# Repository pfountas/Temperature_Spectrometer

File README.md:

# Temperature Spectrometer
Temperature Spectrometer based on the NXP mbed LPC1768 platform.

This is an embedded digital temperature spectrometer with logging capabilities. The system was based on the NXP mbed LPC1768 platform. The microcontroller used in the temperature logger is based on the 32-bit ARM Cortex-M3 microcontroller with 512 kB flash and 64 kB SRAM. The microcontroller was connected to a TMP102 temperature sensor using an I2C interface and to an LCD screen using an SPI interface. The system supports real-time temperature spectrum computation and control and data export through an on-board USB UART connection.

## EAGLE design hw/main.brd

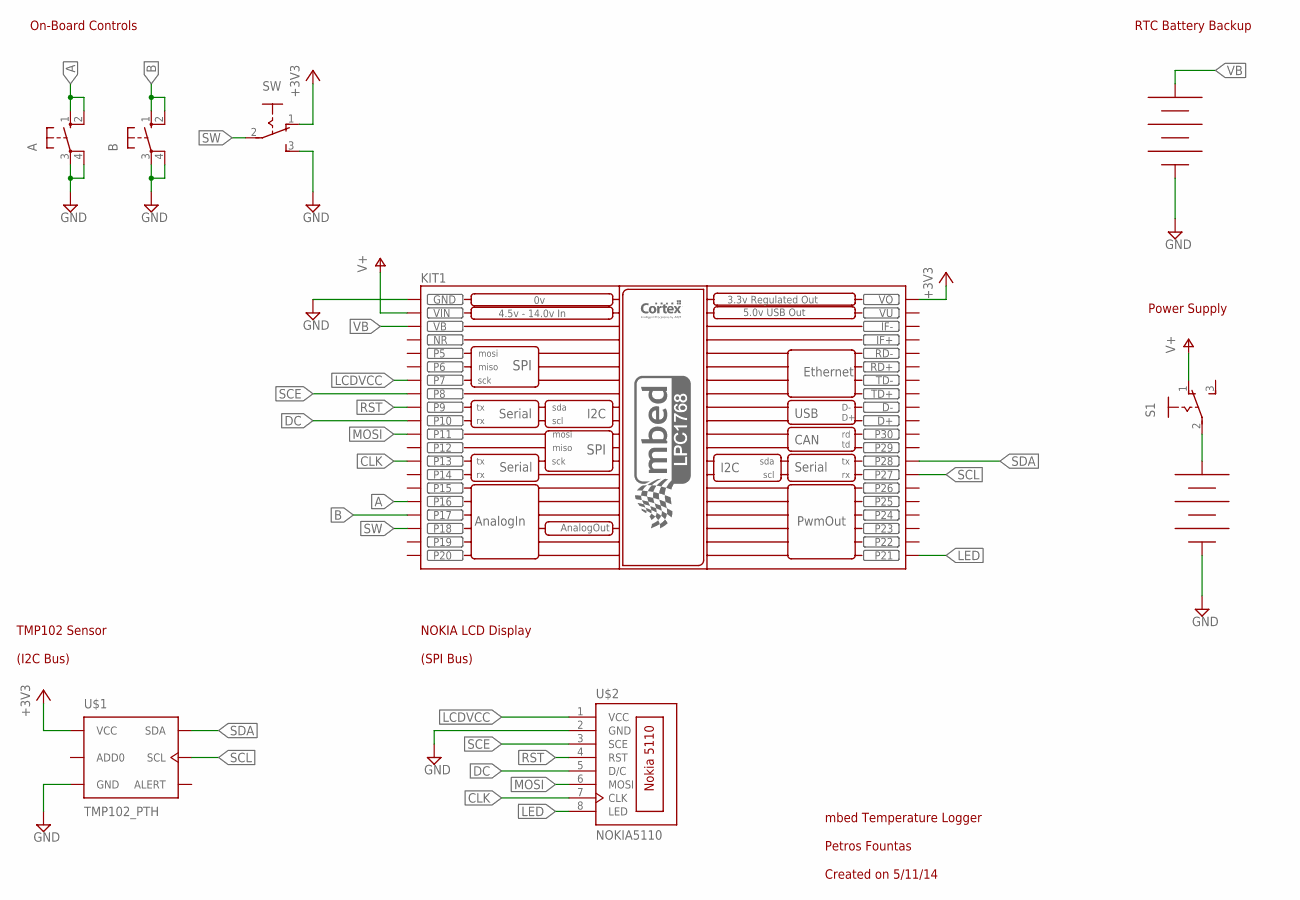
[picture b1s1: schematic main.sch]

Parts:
A: BUTTON_THT; BUTTON
B: BUTTON_THT; BUTTON
BATT1: BATTERY_4AA
BATT2: BATTERY_H_CR2032; BATTERY_H
KIT1: MBED_SILK; MBED
S1: M251
SW: M251
U$1: TMP102_PTH; TMP102
U$2: NOKIA5110

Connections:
+3V3: KIT1.VOUT (VO), SW.1 (O), U$1.VCC
A: A.1 (S), A.2 (S1), KIT1.P$16 (P16)
B: B.1 (S), B.2 (S1), KIT1.P$17 (P17)
CLK: KIT1.P$13 (P13), U$2.7 (CLK)
DC: KIT1.P$10 (P10), U$2.5 (D/C)
GND: A.3, A.4 (P1), B.3, B.4 (P1), BATT1.-, BATT2.-, KIT1.GND, SW.3 (S), U$1.GND, U$2.2 (GND)
LCDVCC: KIT1.P$7 (P7), U$2.1 (VCC)
LED: KIT1.P$21 (P21), U$2.8 (LED)
MOSI: KIT1.P$11 (P11), U$2.6 (MOSI)
unnamed: BATT1.+, S1.2
NR: KIT1.NR
RST: KIT1.P$9 (P9), U$2.4 (RST)
SCE: KIT1.P$8 (P8), U$2.3 (SCE)
SCL: KIT1.P$27 (P27), U$1.SCL
SDA: KIT1.P$28 (P28), U$1.SDA
SW: KIT1.P$18 (P18), SW.2
V+: KIT1.VIN, S1.1 (O)
VB: BATT2.+, KIT1.VB
VU: KIT1.VU

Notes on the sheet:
mbed Temperature Logger Petros Fountas Created on 5/11/14
RTC Battery Backup
Power Supply
TMP102 Sensor (I2C Bus)
NOKIA LCD Display (SPI Bus)
On-Board Controls

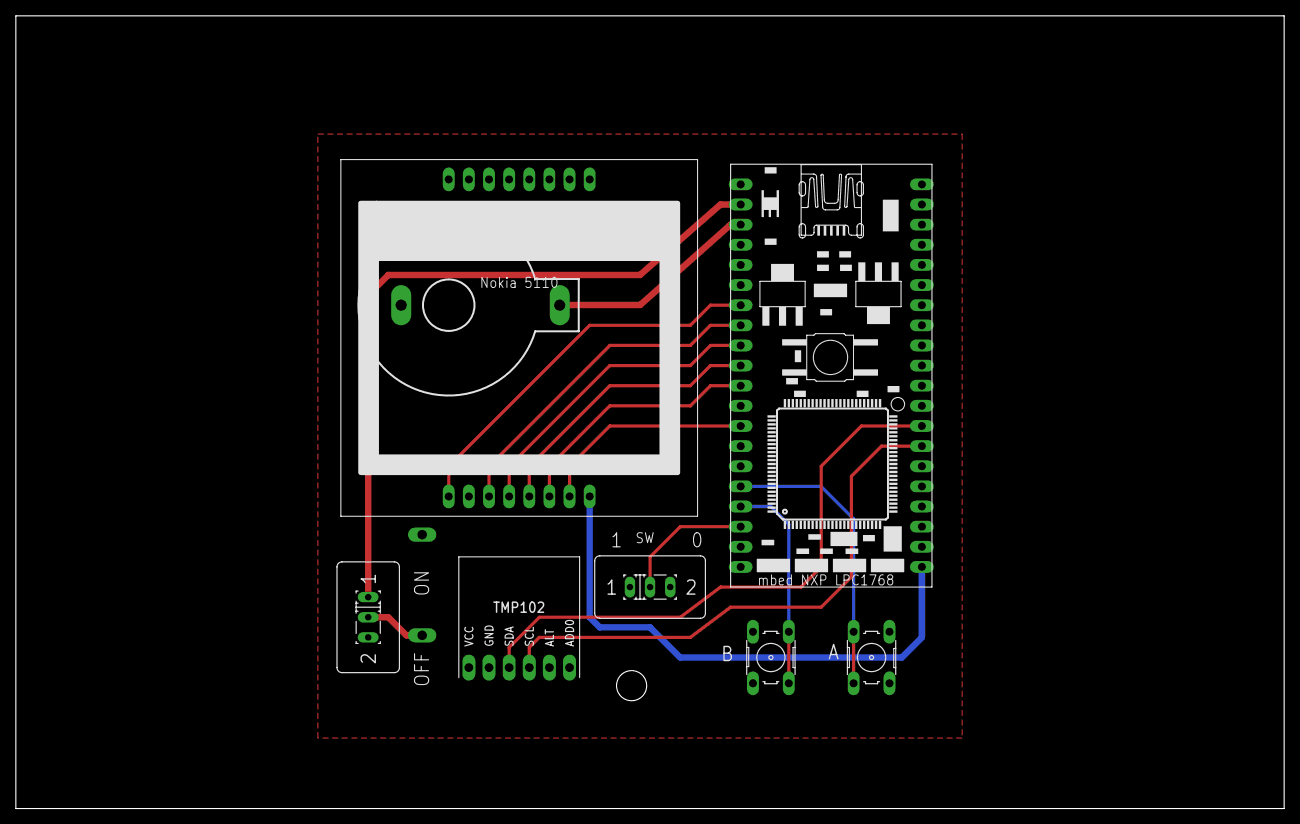
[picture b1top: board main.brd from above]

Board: 2 copper layers, 160.0 x 100.0 mm, 9 parts (1 on the bottom side), 17 nets.

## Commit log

2015-11-07 Initial commit.
2015-11-07 Restructuring
